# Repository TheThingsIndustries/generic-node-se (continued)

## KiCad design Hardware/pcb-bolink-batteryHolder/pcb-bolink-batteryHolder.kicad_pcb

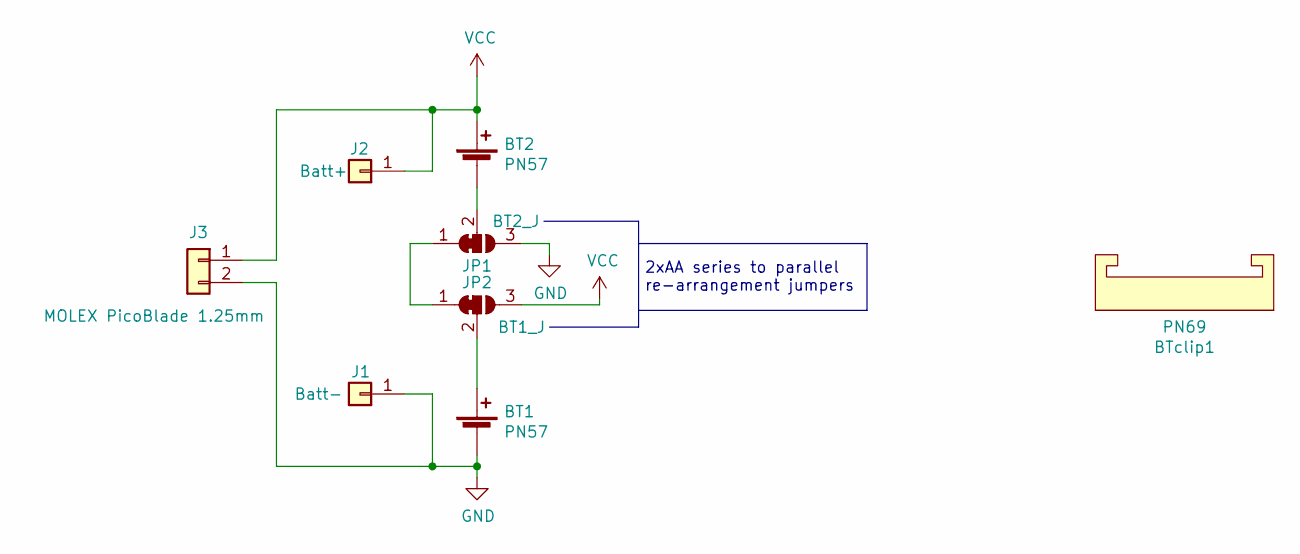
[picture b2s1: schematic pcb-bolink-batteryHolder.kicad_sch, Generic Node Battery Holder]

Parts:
BT1, BT2: PN57; keystone-PN57; MPN 57
BTclip1: PN69; Keystone_69_clip; MPN 69
J1: Batt-; TestPoint_Keystone_5019_Minature; MPN DNM
J2: Batt+; TestPoint_Keystone_5019_Minature; MPN DNM
J3: MOLEX PicoBlade 1.25mm; Molex_PicoBlade_53398-0271_1x02-1MP_P1.25mm_Vertical; MPN 0533980271
JP1: BT2_J; SolderJumper-3_P1.3mm_Bridged2Bar12_Pad1.0x1.5mm_NumberLabe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
JP2: BT1_J; SolderJumper-3_P1.3mm_Bridged2Bar12_Pad1.0x1.5mm_NumberLabe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

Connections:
GND: BT1.2 (-), J1.1, J3.2, JP1.3 (B)
unnamed: BT1.1 (+), JP2.2 (C)
unnamed: BT2.2 (-), JP1.2 (C)
unnamed: JP1.1 (A), JP2.1 (A)
VCC: BT2.1 (+), J2.1, J3.1, JP2.3 (B)

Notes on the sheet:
2xAA series to parallel re-arrangement jumpers

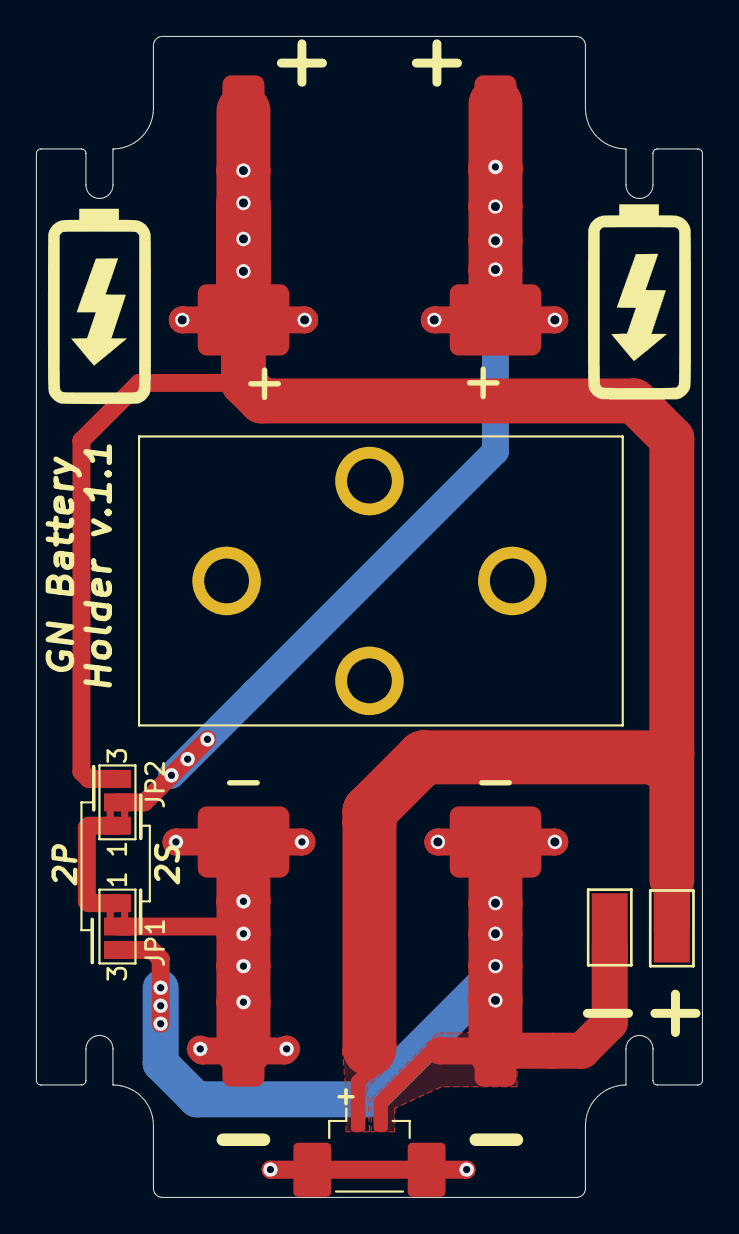
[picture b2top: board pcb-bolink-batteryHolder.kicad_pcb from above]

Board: 2 copper layers, 37.0 x 64.5 mm, 10 parts (0 on the bottom side), 5 nets.

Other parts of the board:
G-BT1, G-BT1#2: LOGO; Icon_Battery_1200px

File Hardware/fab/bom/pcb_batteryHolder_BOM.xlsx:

| Item | Reference | Quantity | Value | MPN | ALT_MPN | Footprint | URL
 |  | BT1, BT2 | 2 | 2xPN57 | 36-57-ND |  | node-lib-v1:keystone-PN57 | https://www.digikey.nl/short/zn47d8
 |  | BTclip1 | 1 | PN69 | 36-69-ND |  | node-lib-v1:Keystone_69_clip | https://www.digikey.nl/short/zn47d7
 |  | J1 | 1 | MOLEX PicoBlade 1.25mm | 533980271 |  | Connector_Molex:Molex_PicoBlade_53398-0271_1x02-1MP_P1.25mm_Vertical | https://lcsc.com/product-detail/Wire-To-Board-Wire-To-Wire-C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
 |  | J2 |  | DNM | ~ |  | TestPoint:TestPoint_Keystone_5019_Minature | ~
 |  | J3 |  | DNM | ~ |  | TestPoint:TestPoint_Keystone_5019_Minature | ~
 | Part: | Generic Node Battery Holder PCB
 | Date: | 10/27/2020
 | Tool: | KiCAD v5.1.8
 | Total Components: | 4
 | Unique Components: | 3

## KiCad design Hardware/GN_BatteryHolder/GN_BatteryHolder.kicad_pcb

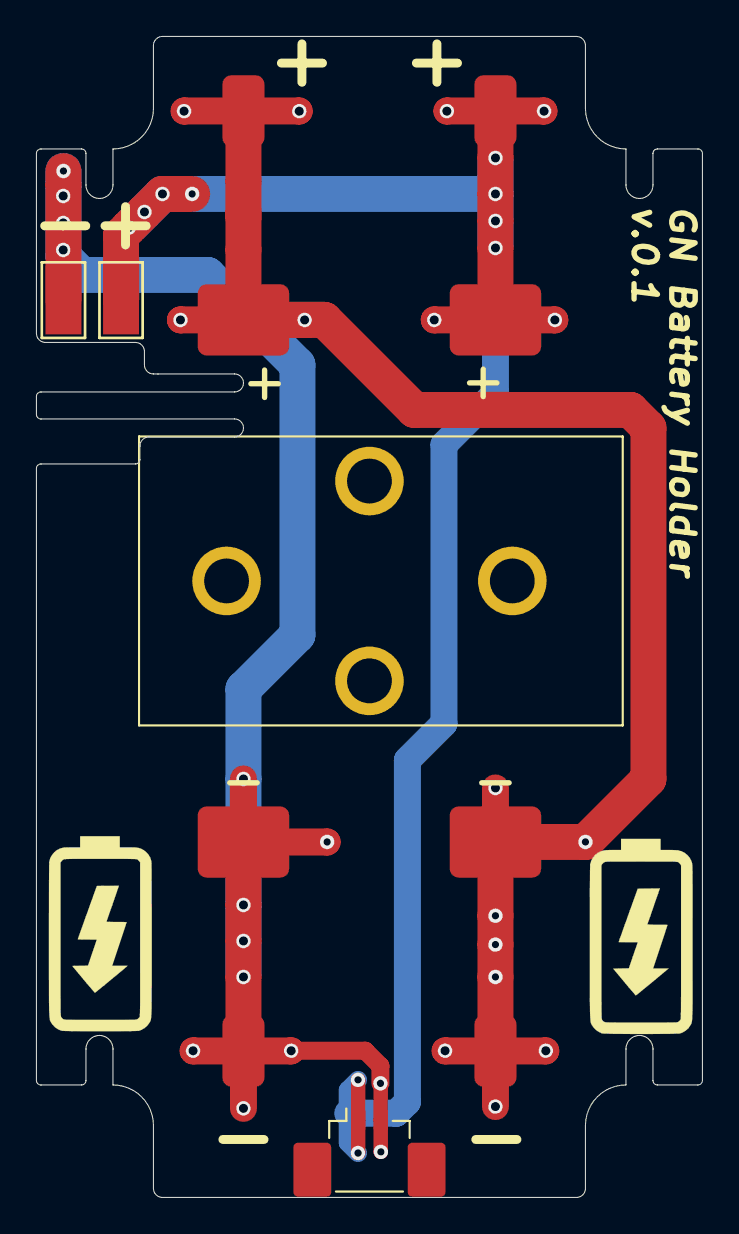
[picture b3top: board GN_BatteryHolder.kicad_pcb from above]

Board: 2 copper layers, 37.0 x 64.5 mm, 6 parts (0 on the bottom side), 3 nets.

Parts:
BT1, BT2: 2xPN57; keystone-PN57
BTclip1: PN69; Keystone_69_clip
J1: Batt-; TestPoint_Keystone_5019_Minature
J2: Batt+; TestPoint_Keystone_5019_Minature
J3: MOLEX PicoBlade 1.25mm; Molex_PicoBlade_53398-0271_1x02-1MP_P1.25mm_Vertical

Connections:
GND: BT2.2, J1.1, J3.2
unnamed: BT1.2, BT2.1
VCC: BT1.1, J2.1, J3.1

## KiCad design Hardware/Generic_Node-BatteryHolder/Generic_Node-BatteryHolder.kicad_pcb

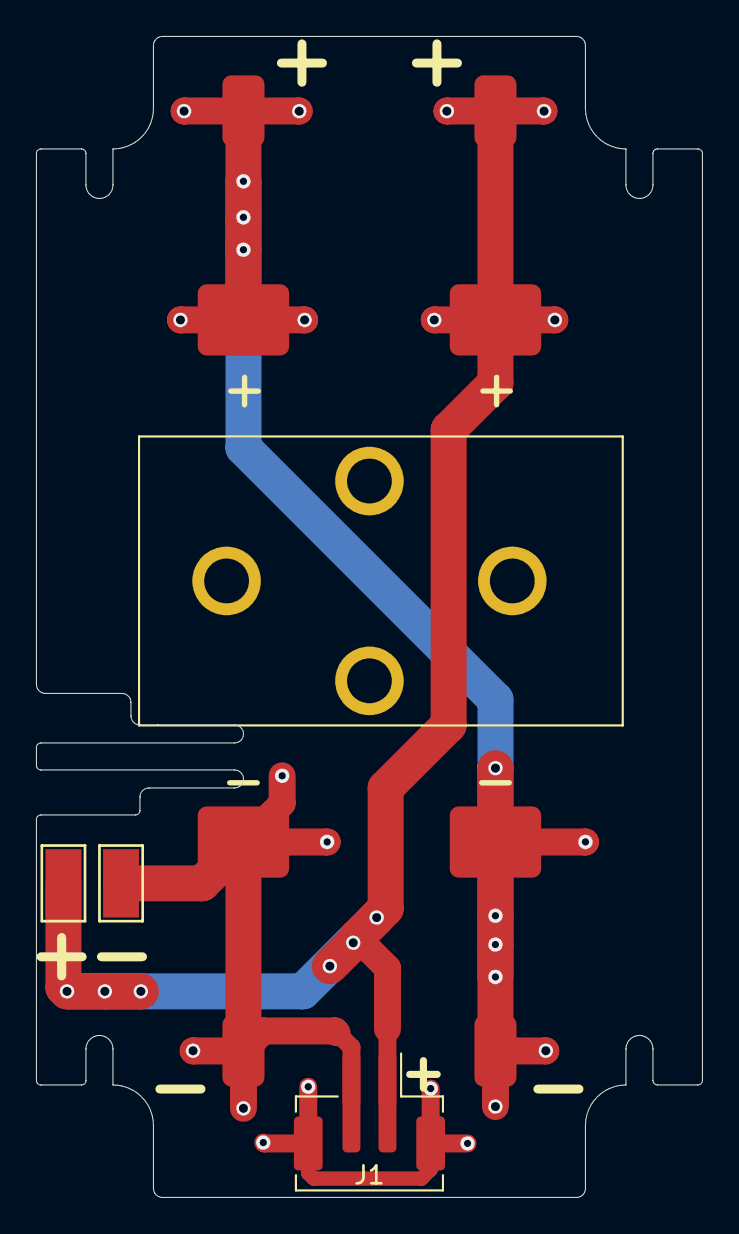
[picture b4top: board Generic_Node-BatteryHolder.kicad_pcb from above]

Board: 2 copper layers, 37.0 x 64.5 mm, 6 parts (0 on the bottom side), 3 nets.

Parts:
BT1, BT2: 2xPN57; keystone-PN57
BTclip1: PN69; Keystone_69_clip
J1: JST-PH-Vertical; JST_PH_B2B-PH-SM4-TB_1x02-1MP_P2.00mm_Vertical
J2: Batt-; TestPoint_Keystone_5019_Minature
J3: Batt+; TestPoint_Keystone_5019_Minature

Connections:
GND: BT2.2, J1.2, J2.1
unnamed: BT1.2, BT2.1
VCC: BT1.1, J1.1, J3.1

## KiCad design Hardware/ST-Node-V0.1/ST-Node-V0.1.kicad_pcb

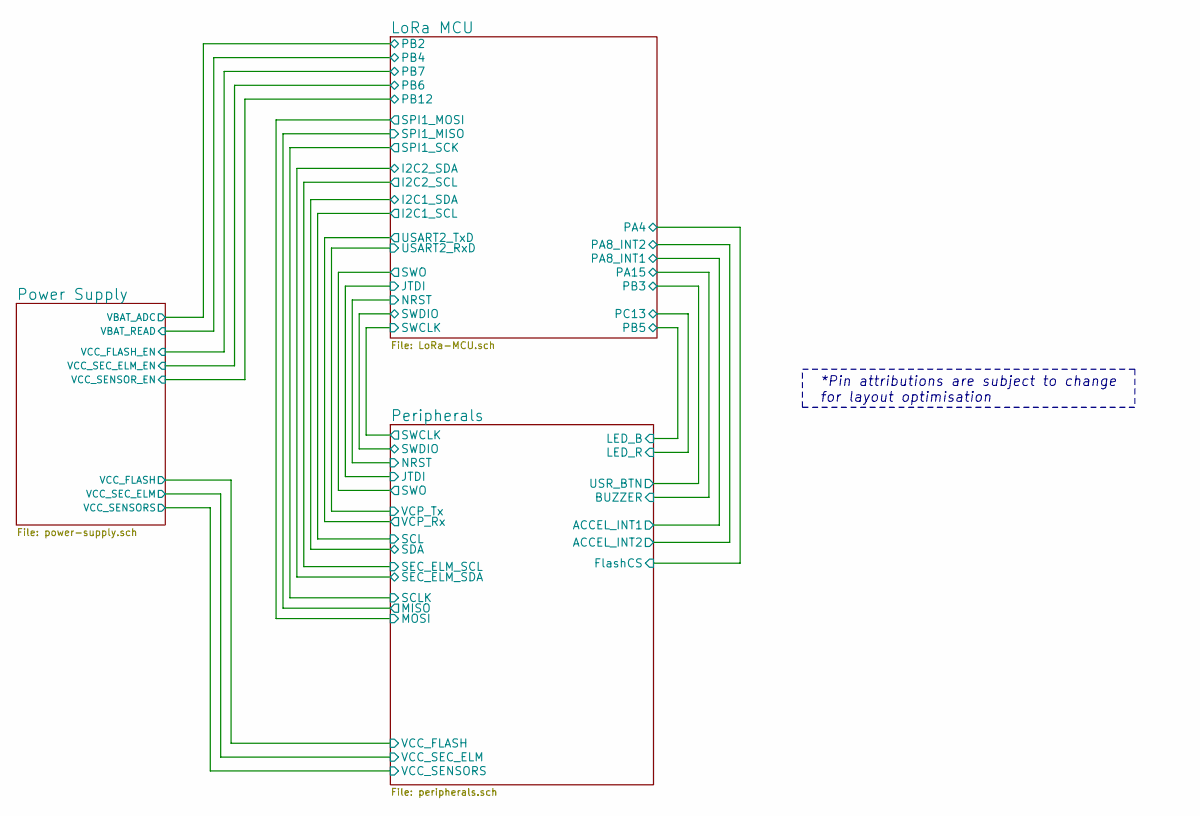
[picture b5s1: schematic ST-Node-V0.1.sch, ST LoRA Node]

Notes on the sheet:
*Pin attributions are subject to change for layout optimisation

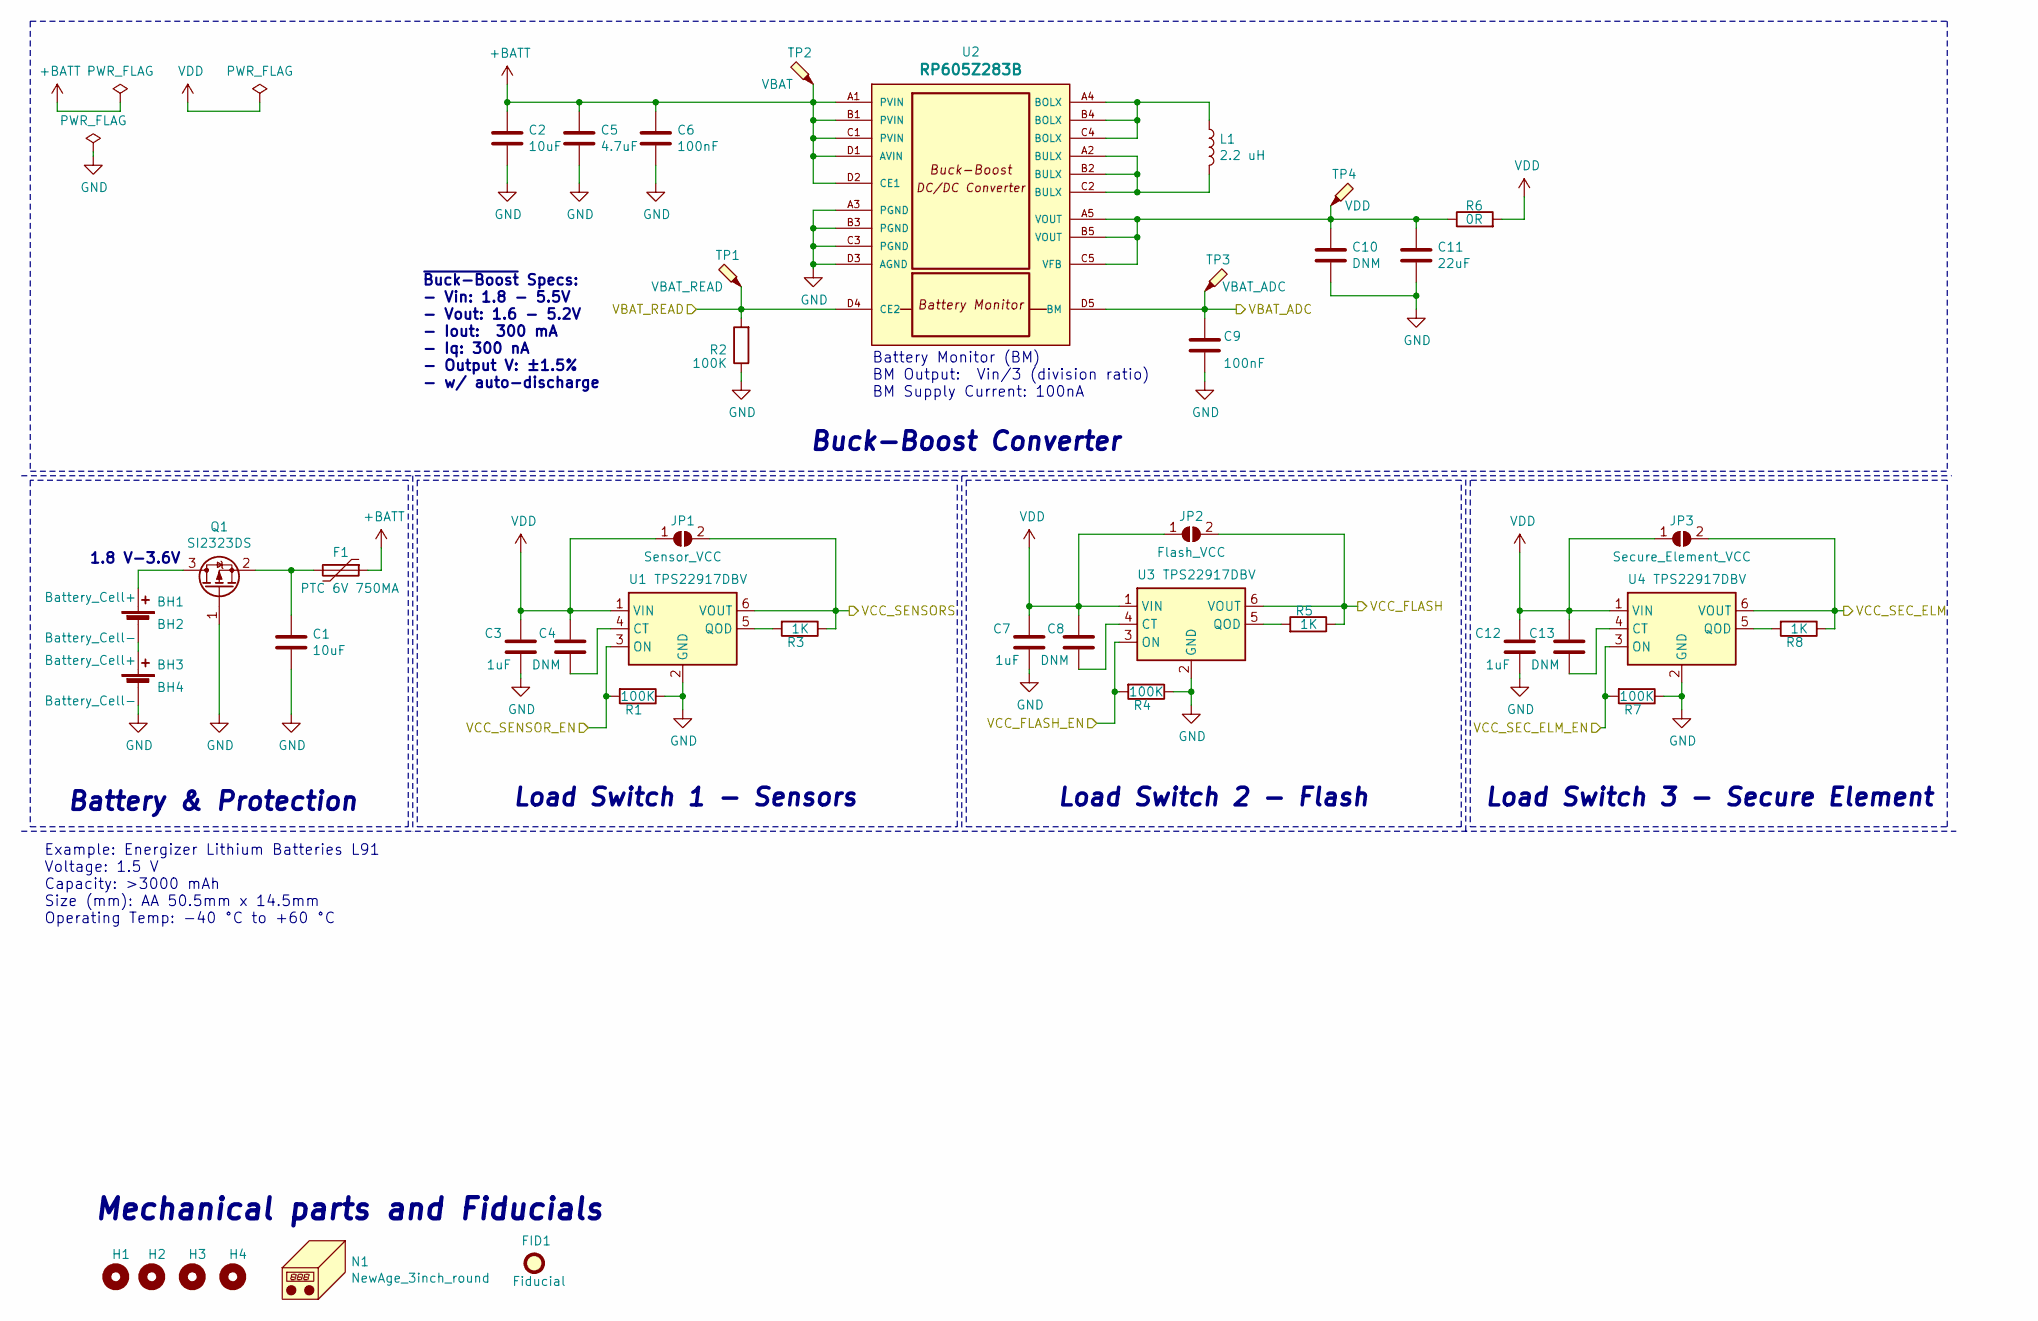
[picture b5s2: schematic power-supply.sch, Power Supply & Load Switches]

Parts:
BH1, BH3: Battery_Cell+; BAT_BK-92; MPN BK-92
BH2, BH4: Battery_Cell-; BAT_BK-92; MPN BK-92
C1, C2: 10uF; C_0603_1608Metric; MPN C1608X5R0J106K080AB
C3, C7, C12: 1uF; C_0402_1005Metric; MPN CL05A105KQ5NNNC
C4, C8, C13: DNM; C_0402_1005Metric
C5: 4.7uF; C_0603_1608Metric; MPN C1608X5R1C475K080AC
C6, C9: 100nF; C_0402_1005Metric; MPN CC0402KRX7R7BB104
C10: DNM; C_0603_1608Metric
C11: 22uF; C_0603_1608Metric; MPN JMK107BBJ226MA
F1: PTC 6V 750MA; Fuse_0805_2012Metric_Castellated; MPN 0ZCK0075FF2E
FID1: Fiducial; Fiducial_0.5mm_Mask1.5mm
H1, H2, H3, H4: MountingHole; MountingHole_2.5mm
JP1: Sensor_VCC; SolderJumper-2_P1.3mm_Open_RoundedPad1.0x1.5mm
JP2: Flash_VCC; SolderJumper-2_P1.3mm_Open_RoundedPad1.0x1.5mm
JP3: Secure_Element_VCC; SolderJumper-2_P1.3mm_Open_RoundedPad1.0x1.5mm
L1: 2.2 uH; L_1008_2520Metric; MPN CVH252009-2R2M
N1: NewAge_3inch_round; MPN S6L-303013
Q1: SI2323DS; SOT-23; MPN SI2323DS-T1-E3
R1, R2, R4, R7: 100K; R_0402_1005Metric; MPN RC0402FR-07100KL
R3, R5, R8: 1K; R_0402_1005Metric; MPN RC0402FR-071KP
R6: 0R; R_0402_1005Metric; MPN RC0402FR-070RL
TP1: VBAT_READ; TestPoint_Pad_D1.0mm
TP2: VBAT; TestPoint_Pad_D1.0mm
TP3: VBAT_ADC; TestPoint_Pad_D1.0mm
TP4: VDD; TestPoint_Pad_D1.0mm
U1, U3, U4: TPS22917DBV; SOT-23-6; MPN TPS22917DBVR
U2: RP605Z283B; WLCSP-20-P3_1.994x1.609mm_Layout5x4_P0.4mm; MPN RP605Z283B-E2-F

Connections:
+BATT: C2.2, C5.1, C6.1, F1.1, TP2.1, U2.A1 (PVIN), U2.B1 (PVIN), U2.C1 (PVIN), U2.D1 (AVIN), U2.D2 (CE1); also elsewhere on the board
/LoRa MCU/PB2: C9.1, TP3.1, U2.D5 (BM); also elsewhere on the board
/LoRa MCU/PB4: R2.2, TP1.1, U2.D4 (CE2); also elsewhere on the board
/LoRa MCU/PB6: R7.2, U4.3 (ON); also elsewhere on the board
/LoRa MCU/PB7: R4.2, U3.3 (ON); also elsewhere on the board
/LoRa MCU/PB12: R1.2, U1.3 (ON); also elsewhere on the board
/Peripherals/VCC_FLASH: JP2.2 (B), R5.1, U3.6 (VOUT); also elsewhere on the board
/Peripherals/VCC_SEC_ELM: JP3.2 (B), R8.1, U4.6 (VOUT); also elsewhere on the board
/Peripherals/VCC_SENSORS: JP1.2 (B), R3.1, U1.6 (VOUT); also elsewhere on the board
GND: BH4.1, C1.1, C2.1, C3.2, C5.2, C6.2, C7.2, C9.2, C10.1, C11.1, C12.2, Q1.1 (G), R1.1, R2.1, R4.1, R7.1, U1.2 (GND), U2.A3 (PGND), U2.B3 (PGND), U2.C3 (PGND), U2.D3 (AGND), U3.2 (GND), U4.2 (GND); also elsewhere on the board
unnamed: BH1.1, Q1.3 (D)
unnamed: BH2.1, BH3.1
unnamed: C1.2, F1.2, Q1.2 (S)
unnamed: C4.2, U1.4 (CT)
unnamed: C8.2, U3.4 (CT)
unnamed: C10.2, C11.2, R6.1, TP4.1, U2.A5 (VOUT), U2.B5 (VOUT), U2.C5 (VFB)
unnamed: C13.2, U4.4 (CT)
unnamed: L1.1, U2.A4 (BOLX), U2.B4 (BOLX), U2.C4 (BOLX)
unnamed: L1.2, U2.A2 (BULX), U2.B2 (BULX), U2.C2 (BULX)
unnamed: R3.2, U1.5 (QOD)
unnamed: R5.2, U3.5 (QOD)
unnamed: R8.2, U4.5 (QOD)

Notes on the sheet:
Example: Energizer Lithium Batteries L91 Voltage: 1.5 V Capacity: >3000 mAh Size (mm): AA 50.5mm x 14.5mm Operating Temp: -40 °C to +60 °C
1.8 V-3.6V
Load Switch 1 - Sensors
Load Switch 2 - Flash
Mechanical parts and Fiducials
Battery & Protection
Load Switch 3 - Secure Element
Buck-Boost Converter
~Buck-Boost Specs: - Vin: 1.8 - 5.5V - Vout: 1.6 - 5.2V - Iout: 300 mA - Iq: 300 nA - Output V: ±1.5% - w/ auto-discharge
Battery Monitor (BM) BM Output: Vin/3 (division ratio) BM Supply Current: 100nA

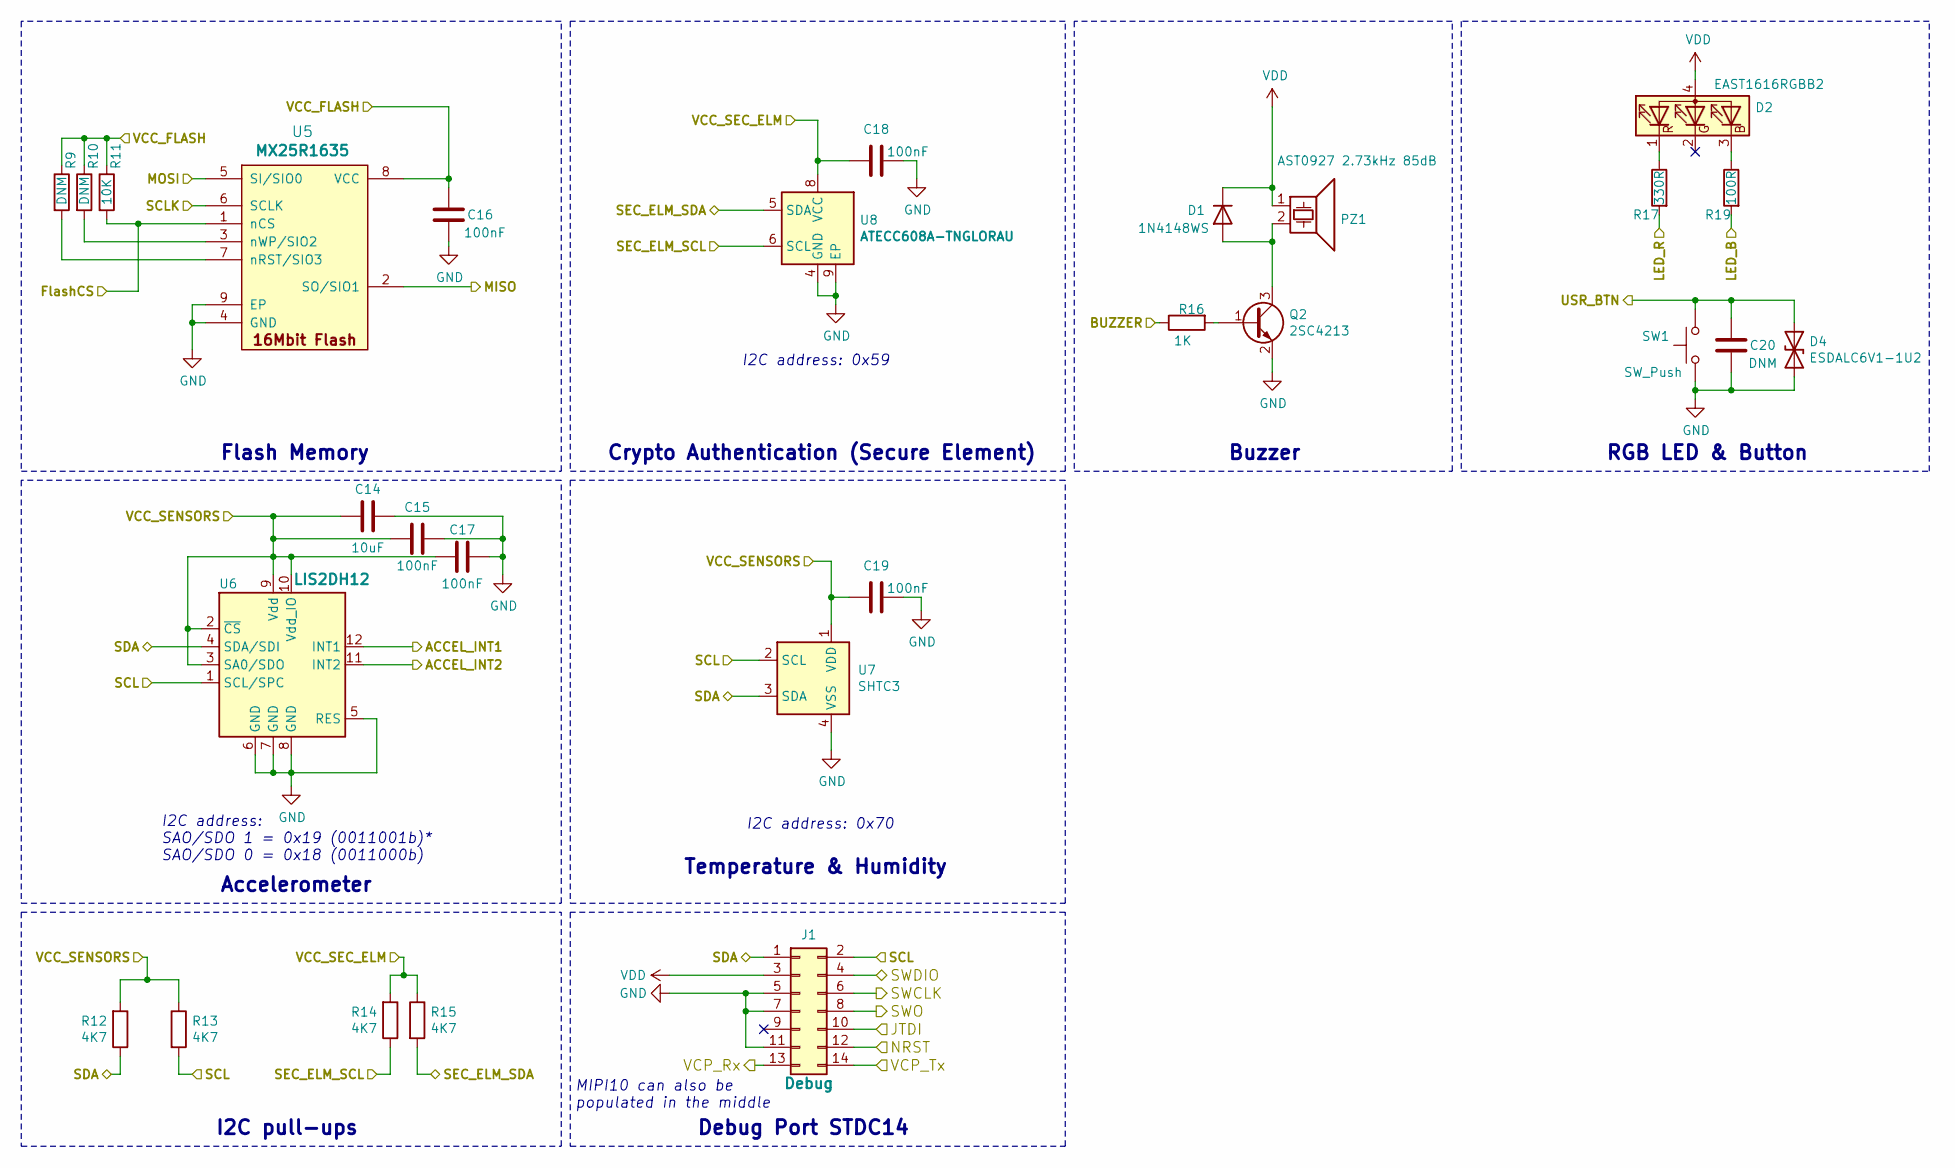
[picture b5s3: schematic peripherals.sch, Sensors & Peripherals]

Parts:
C14: 10uF; C_0603_1608Metric; MPN C1608X5R0J106K080AB
C15, C16, C17, C18, C19: 100nF; C_0402_1005Metric; MPN CC0402KRX7R7BB104
C20: DNM; C_0402_1005Metric
D1: 1N4148WS; D_SOD-323; MPN 1N4148WS-7-F
D2: EAST1616RGBB2; LED_RGB_0606; MPN EAST1616RGBB2
D4: ESDALC6V1-1U2; D_0201_0603Metric; MPN ESDALC6V1-1U2
J1: Debug; PinHeader_2x07_P1.27mm_Vertical_SMD; MPN FTSH-107-01-F-DV-K
PZ1: AST0927 2.73kHz 85dB; Buzzer_AST0927MW-3.6TRQ; MPN AST0927MW-3.6TRQ
Q2: 2SC4213; SOT-323_SC-70; MPN 2SC4213BTE85LF
R9, R10: DNM; R_0402_1005Metric; MPN DNM
R11: 10K; R_0402_1005Metric; MPN AC0402JR-0710KL
R12, R13, R14, R15: 4K7; R_0402_1005Metric; MPN AC0402FR-074K7L
R16: 1K; R_0402_1005Metric; MPN RC0402FR-071KP
R17: 330R; R_0402_1005Metric; MPN AC0402FR-07330RL
R19: 100R; R_0402_1005Metric; MPN RC0402FR-07100RL
SW1: SW_Push; EVQ-P2R02W; MPN EVQ-P2R02W
U5: MX25R1635; FLASH_UFDFN-8-MX25R1635F; MPN MX25R1635FZUIL0
U6: LIS2DH12; LGA-12_2x2mm_P0.5mm; MPN LIS2DH12TR
U7: SHTC3; Sensirion_DFN-4-1EP_2x2mm_P1mm_EP0.7x1.6mm; MPN SHTC3
U8: ATECC608A-TNGLORAU; DFN-8-1EP_3x2mm_P0.5mm_EP1.3x1.5mm; MPN ATECC608A-TNGLORAU-B

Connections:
/LoRa MCU/I2C1_SCL: J1.2, R13.2, U6.1 (SCL/SPC), U7.2 (SCL); also elsewhere on the board
/LoRa MCU/I2C1_SDA: J1.1, R12.1, U6.4 (SDA/SDI), U7.3 (SDA); also elsewhere on the board
/LoRa MCU/I2C2_SCL: R14.1, U8.6 (SCL); also elsewhere on the board
/LoRa MCU/I2C2_SDA: R15.2, U8.5 (SDA); also elsewhere on the board
/LoRa MCU/JTDI: J1.10; also elsewhere on the board
/LoRa MCU/PB3: C20.2, D4.1 (A1), SW1.2; also elsewhere on the board
/LoRa MCU/SWCLK: J1.6; also elsewhere on the board
/LoRa MCU/SWDIO: J1.4; also elsewhere on the board
/LoRa MCU/SWO: J1.8; also elsewhere on the board
/LoRa MCU/USART2_RxD: J1.14; also elsewhere on the board
/LoRa MCU/USART2_TxD: J1.13; also elsewhere on the board
/Peripherals/ACCEL_INT1: U6.12 (INT1); also elsewhere on the board
/Peripherals/ACCEL_INT2: U6.11 (INT2); also elsewhere on the board
/Peripherals/BUZZER: R16.1; also elsewhere on the board
/Peripherals/FlashCS: R11.2, U5.1 (nCS); also elsewhere on the board
/Peripherals/LED_B: R19.2; also elsewhere on the board
/Peripherals/LED_R: R17.2; also elsewhere on the board
/Peripherals/MISO: U5.2 (SO/SIO1); also elsewhere on the board
/Peripherals/MOSI: U5.5 (SI/SIO0); also elsewhere on the board
/Peripherals/SCLK: U5.6 (SCLK); also elsewhere on the board
/Peripherals/VCC_FLASH: C16.2, R9.1, R10.1, R11.1, U5.8 (VCC); also elsewhere on the board
/Peripherals/VCC_SEC_ELM: C18.2, R14.2, R15.1, U8.8 (VCC); also elsewhere on the board
/Peripherals/VCC_SENSORS: C14.2, C15.2, C17.2, C19.2, R12.2, R13.1, U6.2 (~CS), U6.3 (SA0/SDO), U6.9 (Vdd), U6.10 (Vdd_IO), U7.1 (VDD); also elsewhere on the board
GND: C14.1, C15.1, C16.1, C17.1, C18.1, C19.1, C20.1, D4.2 (A2), J1.5, J1.7, J1.11, Q2.2 (E), SW1.1, U5.4 (GND), U5.9 (EP), U6.5 (RES), U6.6 (GND), U6.7 (GND), U6.8 (GND), U7.4 (VSS), U8.4 (GND), U8.9 (EP); also elsewhere on the board
NRST: J1.12; also elsewhere on the board
unnamed: D1.2 (A), PZ1.2, Q2.3 (C)
unnamed: D2.1 (RK), R17.1
unnamed: D2.3 (BK), R19.1
unnamed: Q2.1 (B), R16.2
unnamed: R9.2, U5.7 (nRST/SIO3)
unnamed: R10.2, U5.3 (nWP/SIO2)

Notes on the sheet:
I2C address: SAO/SDO 1 = 0x19 (0011001b)* SAO/SDO 0 = 0x18 (0011000b)
Accelerometer
Flash Memory
Crypto Authentication (Secure Element)
RGB LED & Button
Buzzer
I2C address: 0x59
Temperature & Humidity
I2C address: 0x70
I2C pull-ups
MIPI10 can also be populated in the middle
Debug Port STDC14

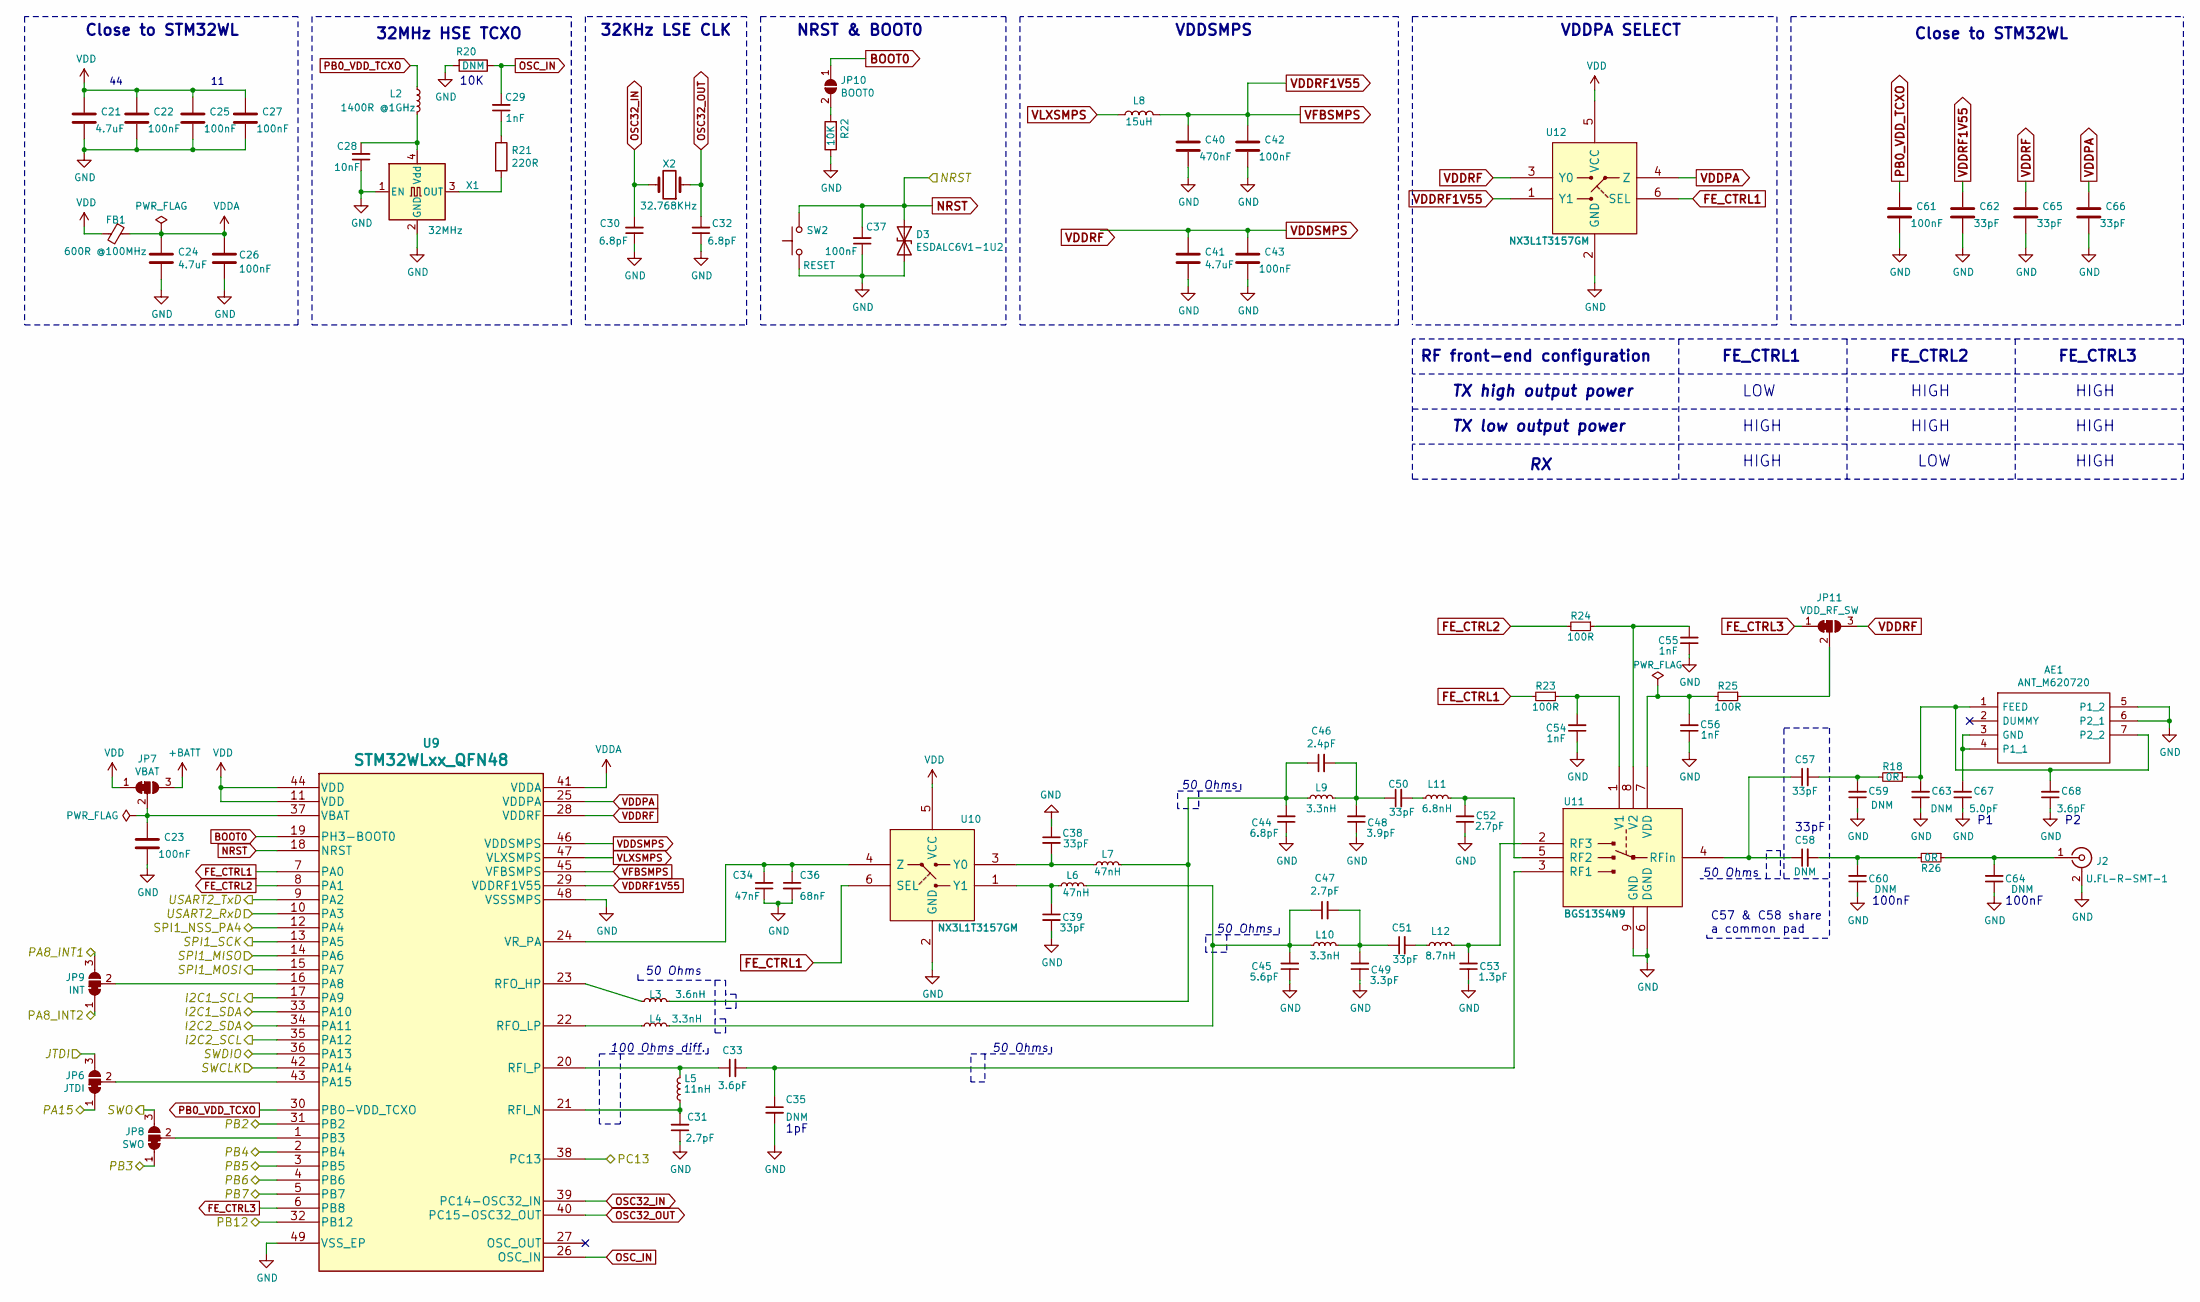
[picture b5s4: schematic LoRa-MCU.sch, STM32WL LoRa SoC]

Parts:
AE1: ANT_M620720; MPN M620720; Mouser Part Number 581-M620720
C21, C24, C41: 4.7uF; C_0603_1608Metric; MPN C1608X5R1C475K080AC
C22, C23, C25, C26, C27, C37, C42, C43, C61: 100nF; C_0402_1005Metric; MPN CC0402KRX7R7BB104
C28: 10nF; C_0402_1005Metric; MPN CC0402KRX7R7BB103
C29, C54, C55, C56: 1nF; C_0402_1005Metric; MPN CC0402KRX7R7BB102
C30, C32, C44: 6.8pF; C_0402_1005Metric; MPN GRM1555C1H6R8BA01D
C31, C47, C52: 2.7pF; C_0402_1005Metric; MPN CC0402BRNPO9BN2R7
C33, C68: 3.6pF; C_0402_1005Metric; MPN CC0402BRNPO9BN3R6
C34: 47nF; C_0402_1005Metric; MPN CC0402KRX7R8BB473
C35, C58, C59, C60, C63, C64: DNM; C_0402_1005Metric
C36: 68nF; C_0402_1005Metric; MPN CC0402JRNPO9BN680
C38, C39, C50, C51, C57, C62, C65, C66: 33pF; C_0402_1005Metric; MPN CC0402JRNPO9BN330
C40: 470nF; C_0603_1608Metric; MPN CC0603KRX5R7BB474
C45: 5.6pF; C_0402_1005Metric; MPN CC0402BRNPO9BN5R6
C46: 2.4pF; C_0402_1005Metric; MPN CC0402BRNPO9BN2R4
C48: 3.9pF; C_0402_1005Metric; MPN CC0402BRNPO9BN3R9
C49: 3.3pF; C_0402_1005Metric; MPN CC0402BRNPO9BN3R3
C53: 1.3pF; C_0402_1005Metric; MPN CC0402BRNPO9BN1R3
C67: 5.0pF; C_0402_1005Metric; MPN GJM1555C1H5R0WB01D
D3: ESDALC6V1-1U2; D_0201_0603Metric; MPN ESDALC6V1-1U2
FB1: 600R @100MHz; L_0603_1608Metric; MPN BLM18AG601SN1D
J2: U.FL-R-SMT-1; U.FL_Hirose_U.FL-R-SMT-1_Vertical; MPN U.FL-R-SMT-1
JP6: JTDI; SolderJumper-3_P1.3mm_Bridged12_RoundedPad1.0x1.5mm_NumberL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
JP7: VBAT; SolderJumper-3_P1.3mm_Bridged12_RoundedPad1.0x1.5mm_NumberL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
JP8: SWO; SolderJumper-3_P1.3mm_Bridged12_RoundedPad1.0x1.5mm_NumberL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
JP9: INT; SolderJumper-3_P1.3mm_Bridged12_RoundedPad1.0x1.5mm_NumberL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
JP10: BOOT0; SW_SPST_B3U-1000P
JP11: VDD_RF_SW; SolderJumper-3_P1.3mm_Bridged12_RoundedPad1.0x1.5mm_NumberL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
L2: 1400R @1GHz; L_0402_1005Metric; MPN BLM15HG102SN1#
L3: 3.6nH; L_0402_1005Metric; MPN LQW15AN3N6C10
L4, L9, L10: 3.3nH; L_0402_1005Metric; MPN LQW15AN3N3D10
L5: 11nH; L_0402_1005Metric; MPN LQW15AN11NG00
L6, L7: 47nH; L_0402_1005Metric; MPN LQW15AN47NJ00#
L8: 15uH; L_0805_2012Metric; MPN MLZ2012M150W
L11: 6.8nH; L_0402_1005Metric; MPN LQW15AN6N8H00
L12: 8.7nH; L_0402_1005Metric; MPN LQW15AN8N7H00
R18, R26: 0R; R_0402_1005Metric; MPN RC0402FR-070RL
R20: DNM; L_0402_1005Metric
R21: 220R; L_0402_1005Metric; MPN RC0402FR-07220RL
R22: 10K; L_0402_1005Metric; MPN AC0402JR-0710KL
R23, R24, R25: 100R; R_0402_1005Metric; MPN RC0402FR-07100RL
SW2: RESET; EVQ-P2R02W; MPN EVQ-P2R02W
U9: STM32WLxx_QFN48; QFN-48-1EP_7x7mm_P0.5mm_EP5.45x5.45mm_ThermalVias; MPN STM32WLxx_QFN48
U10, U12: NX3L1T3157GM; 6-XFDFN_SOT-886; MPN NX3L1T3157GM
U11: BGS13S4N9; RFSW_BGS13S4N9E6327XTSA1; MPN BGS13S4N9E6327XTSA1
X1: 32MHz; TCXO_NT2016SA-32M-END4263A; MPN NT2016SA-32M-END4263A
X2: 32.768KHz; Crystal_SMD_NX2012SA_32.768KHz; MPN NX2012SA-32.768KHZ-EXS00A-MU00527

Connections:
+BATT: JP7.3 (B); also elsewhere on the board
/LoRa MCU/I2C1_SCL: U9.17 (PA9); also elsewhere on the board
/LoRa MCU/I2C1_SDA: U9.33 (PA10); also elsewhere on the board
/LoRa MCU/I2C2_SCL: U9.35 (PA12); also elsewhere on the board
/LoRa MCU/I2C2_SDA: U9.34 (PA11); also elsewhere on the board
/LoRa MCU/JTDI: JP6.3 (B); also elsewhere on the board
/LoRa MCU/PB2: U9.31 (PB2); also elsewhere on the board
/LoRa MCU/PB3: JP8.1 (A); also elsewhere on the board
/LoRa MCU/PB4: U9.2 (PB4); also elsewhere on the board
/LoRa MCU/PB6: U9.4 (PB6); also elsewhere on the board
/LoRa MCU/PB7: U9.5 (PB7); also elsewhere on the board
/LoRa MCU/PB12: U9.32 (PB12); also elsewhere on the board
/LoRa MCU/RFI_P: C33.1, L5.2, U9.20 (RFI_P)
/LoRa MCU/SWCLK: U9.42 (PA14); also elsewhere on the board
/LoRa MCU/SWDIO: U9.36 (PA13); also elsewhere on the board
/LoRa MCU/SWO: JP8.3 (B); also elsewhere on the board
/LoRa MCU/USART2_RxD: U9.10 (PA3); also elsewhere on the board
/LoRa MCU/USART2_TxD: U9.9 (PA2); also elsewhere on the board
/Peripherals/ACCEL_INT1: JP9.3 (B); also elsewhere on the board
/Peripherals/ACCEL_INT2: JP9.1 (A); also elsewhere on the board
/Peripherals/BUZZER: JP6.1 (A); also elsewhere on the board
/Peripherals/FlashCS: U9.12 (PA4); also elsewhere on the board
/Peripherals/LED_B: U9.3 (PB5); also elsewhere on the board
/Peripherals/LED_R: U9.38 (PC13); also elsewhere on the board
/Peripherals/MISO: U9.14 (PA6); also elsewhere on the board
/Peripherals/MOSI: U9.15 (PA7); also elsewhere on the board
/Peripherals/SCLK: U9.13 (PA5); also elsewhere on the board
BOOT0: JP10.1 (A), U9.19 (PH3-BOOT0)
FE_CTRL1: R23.2, U9.7 (PA0), U10.6 (SEL), U12.6 (SEL)
FE_CTRL2: R24.2, U9.8 (PA1)
FE_CTRL3: JP11.1 (A), U9.6 (PB8)
GND: AE1.5 (P1_2), AE1.6 (P2_1), C21.2, C22.2, C23.2, C24.2, C25.2, C26.2, C27.2, C28.1, C30.1, C31.1, C32.1, C34.1, C35.2, C36.2, C37.1, C38.1, C39.2, C40.2, C41.2, C42.2, C43.2, C44.1, C45.1, C48.1, C49.1, C52.1, C53.1, C54.1, C55.1, C56.1, C59.1, C60.1, C61.2, C62.2, C63.1, C64.1, C65.2, C66.2, C67.1, C68.1, D3.2 (A2), J2.2 (Ext), R20.2, R22.1, SW2.1, U9.48 (VSSSMPS), U9.49 (VSS_EP), U10.2 (GND), U11.6 (DGND), U11.9 (GND), U12.2 (GND), X1.1 (EN), X1.2 (GND); also elsewhere on the board
NRST: C37.2, D3.1 (A1), SW2.2, U9.18 (NRST); also elsewhere on the board
unnamed: AE1.1 (FEED), AE1.7 (P2_2), C63.2, C68.2, R18.1
unnamed: AE1.3 (GND), AE1.4 (P1_1), C67.2
unnamed: C23.1, JP7.2 (C), U9.37 (VBAT)
unnamed: C28.2, L2.2, X1.4 (Vdd)
unnamed: C29.1, R21.1
unnamed: C31.2, L5.1, U9.21 (RFI_N)
unnamed: C33.2, C35.1, U11.3 (RF1)
unnamed: C34.2, C36.1, U9.24 (VR_PA), U10.4 (Z)
unnamed: C38.2, L7.1, U10.3 (Y0)
unnamed: C39.1, L6.1, U10.1 (Y1)
unnamed: C44.2, C46.1, L3.2, L7.2, L9.1
unnamed: C45.2, C47.1, L4.2, L6.2, L10.1
unnamed: C46.2, C48.2, C50.1, L9.2
unnamed: C47.2, C49.2, C51.1, L10.2
unnamed: C50.2, L11.1
unnamed: C51.2, L12.1
unnamed: C52.2, L11.2, U11.5 (RF2)
unnamed: C53.2, L12.2, U11.2 (RF3)
unnamed: C54.2, R23.1, U11.1 (V1)
unnamed: C55.2, R24.1, U11.8 (V2)
unnamed: C56.2, R25.2, U11.7 (VDD)
unnamed: C57.1, C58.1, U11.4 (RFin)
unnamed: C57.2, C59.2, R18.2
unnamed: C58.2, C60.2, R26.2
unnamed: C64.2, J2.1 (In), R26.1
unnamed: JP6.2 (C), U9.43 (PA15)
unnamed: JP8.2 (C), U9.1 (PB3)
unnamed: JP9.2 (C), U9.16 (PA8)
unnamed: JP10.2 (B), R22.2
unnamed: JP11.2 (C), R25.1
unnamed: L3.1, U9.23 (RFO_HP)
unnamed: L4.1, U9.22 (RFO_LP)
unnamed: R21.2, X1.3 (OUT)
OSC32_IN: C30.2, U9.39 (PC14-OSC32_IN), X2.2
OSC32_OUT: C32.2, U9.40 (PC15-OSC32_OUT), X2.1
OSC_IN: C29.2, R20.1, U9.26 (OSC_IN)
PB0_VDD_TCXO: C61.1, L2.1, U9.30 (PB0-VDD_TCXO)
VDDA: C24.1, C26.1, FB1.1, U9.41 (VDDA)
VDDPA: C66.1, U9.25 (VDDPA), U12.4 (Z)
VDDRF1V55: C40.1, C42.1, C62.1, L8.2, U9.29 (VDDRF1V55), U9.45 (VFBSMPS), U12.1 (Y1)
VLXSMPS: L8.1, U9.47 (VLXSMPS)

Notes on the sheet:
32MHz HSE TCXO
32KHz LSE CLK
NRST & BOOT0
VDDSMPS
VDDPA SELECT
Close to STM32WL
FE_CTRL1
FE_CTRL2
FE_CTRL3
RF front-end configuration
TX high output power
TX low output power
LOW
HIGH
100 Ohms diff.
50 Ohms
1pF
33pF
100nF
C57 & C58 share a common pad
10K

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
